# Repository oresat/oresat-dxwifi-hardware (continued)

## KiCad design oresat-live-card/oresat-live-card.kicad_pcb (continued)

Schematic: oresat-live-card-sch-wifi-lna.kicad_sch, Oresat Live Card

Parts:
C90, C91, C93: 15p; 0402-C-NOSILK; MPN GJM1555C1H150JB01D
C92: 1u; 0603-C-NOSILK; MPN GRT188R71E105KE13D
C106, C111: 100n; 0603-C-NOSILK; MPN C0603C104K5RACAUTO
C107, C114: 100p; 0402-C-NOSILK; MPN GCM1555C1H101GA16D
C108: 1n; 0402-C-NOSILK; MPN C0402C102J1GACTU
C109: 1n; 0402-C-NOSILK; MPN CGA2B2NP01H102J050BA
C110: 1p; 0402-C-NOSILK; MPN GCM1555C1H1R0CA16J
C112, C113: 100n; 0402-C-NOSILK; MPN CGA2B3X7R1E104K050BB
D15: GRN; LED-0603; MPN 150060GS75000
FL1, FL2: QPQ1907SR; MPN QPQ1907SR
L3: 18n; 0603-C-NOSILK; MPN 0603DC-18NXJRW
L4: 1.5n; 0402-C-NOSILK; MPN 0402HM-1N5EKTS
R85: 4.7k; 0603-C-NOSILK; MPN RMCF0603FT4K70
R88: 10k; 0603-C-NOSILK; MPN RMCF0603FT10K0
R105: 33k; 0603-C-NOSILK; MPN RMCF0603FT33K0
R106: 0; 0402-C-NOSILK; MPN RMCF0402ZT0R00
R109: 56; 0603-C-NOSILK; MPN ERJ-3EKF56R0V
R118, R119, R120: 4.99k; 0603-C-NOSILK; MPN RMCF0603FT4K99
R121: 100; 0603-C-NOSILK; MPN RMCF0603FT100R
TP26: TEST-POINT3X4; TestPoint-0.75mm-th
U18: TQP3M9037; DFN-8-1EP_2x2mm_P0.5mm_EP0.8x1.6mm; MPN TQP3M9037
U27: PAT1220-C-3DB; RF_Attenuator_Susumu_PAT1220; MPN PAT1220-C-3DB-T5
U28: PD2328J5050S2HF; MPN PD2328J5050S2HF
U29: LTC5538; DFN-8-1EP_3x3mm_P0.5mm_EP1.65x2.38mm; MPN LT5538IDD#TRPBF

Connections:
5VA: C106.2, C107.1, C112.2, C113.2, C114.1, R106.2, R118.1, U29.5 (VCC); also elsewhere on the board
/SIP B: ADC + Crystals/RF/RX_IN_DETECTED: C111.1, R119.2, R120.2, TP26.1 (1_1); also elsewhere on the board
/WiFi LNA/AR9271_RX: R121.1, U28.4 (OUTPUT1); also elsewhere on the board
/WiFi LNA/LNA_SHUTDOWN: R85.1, R105.1; also elsewhere on the board
/WiFi LNA/RX_FROM_SWITCH: FL1.1 (INPUT); also elsewhere on the board
GND: C91.2, C92.2, C106.1, C107.2, C108.2, C110.1, C111.2, C114.2, D15.1 (K), FL1.2 (GND), FL1.3 (GND), FL1.5 (GND), FL2.2 (GND), FL2.3 (GND), FL2.5 (GND), R88.2, R109.2, R120.1, U18.9 (GND), U27.3, U28.1 (GND), U28.3 (GND), U28.5 (GND), U29.4 (GND), U29.9 (GND); also elsewhere on the board
unnamed: C91.1, C92.1, L3.1, R106.1
unnamed: C93.2, U27.1
unnamed: C109.1, L4.2, R109.1
unnamed: D15.2 (A), R85.2
unnamed: C90.1, FL1.4 (OUTPUT)
unnamed: FL2.1 (INPUT), U27.2
unnamed: FL2.4 (OUTPUT), U28.2 (INPUT)
unnamed: C90.2, U18.2 (RF_IN)
unnamed: C93.1, L3.2, U18.7 (RF_OUT)
unnamed: R88.1, R105.2, U18.6 (SHUT_DOWN)
unnamed: C110.2, L4.1, R121.2, U28.6 (OUTPUT2)
unnamed: C113.1, U29.7 (CAP+)
unnamed: C112.1, U29.6 (CAP-)
unnamed: R118.2, U29.1 (EN)
unnamed: C109.2, U29.2 (IN+)
unnamed: C108.1, U29.3 (IN-)
unnamed: R119.1, U29.8 (OUT)

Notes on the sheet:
~ 1.65 V max which is < 1.8 V of Octavo ADC max
0402
Changed from 100 to 56
~ 3 V max
RF Detector, transforms RF detected into a DC sense line for Octavo to read
All resistors 0603 +/- 1% unless marked and AEQ certified unless otherwise marked. All caps are 0603 10% X5R or better and Vw >= 25 V and AEQ certified unless otherwise marked.
"LNA OFF"

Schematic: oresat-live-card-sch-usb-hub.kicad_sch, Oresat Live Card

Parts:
C1, C27, C28, C42, C54, C55, C56, C57, C58, C59, C60, C65, C66, C67, C68, C70, C71, C72: 100n; 0603-C-NOSILK; MPN C0603C104K5RACAUTO
C53, C69, C76, C96, C97: 10u; 0805-C-NOSILK; MPN GRT21BC71E106KE13K
C63, C64: 18p; 0603-C-NOSILK; MPN C0603C120J1GACTU
C73: 1u; 0603-C-NOSILK; MPN GRT188R71E105KE13D
D10: GRN; LED-0603; MPN 150060GS75000
FB1, FB3: BLM18KG300JH1D; 0603; MPN BLM18KG300JH1D
FB4, FB5: MMZ1608Y221BTD25; 0603; MPN MMZ1608Y221BTD25
R6, R7, R21, R59, R76, R77, R79, R89, R90, R91: 10k; 0603-C-NOSILK; MPN RMCF0603FT10K0
R29: 4.7k; 0603-C-NOSILK; MPN RMCF0603FT4K70
R78: 9.53k; 0603-C-NOSILK; MPN RMCF0603FT9K53
R83: 90.9k; 0603-C-NOSILK; MPN RMCF0603FT90K9
R98, R99: 0; 0603-C-NOSILK; MPN RMCF0603ZT0R00
TP1, TP15: TEST-POINT; TestPoint_Pad_D1.0mm
TP16, TP17, TP18: TEST-POINT3X4; TestPoint_Pad_D1.0mm
U2: TUSB4020BI; TQFP-48-1EP_7x7mm_P0.5mm_EP5x5mm; MPN TUSB4020BIPHPRQ1
U9, U20: TPS2041BQDBVRQ1; DBV5; MPN TPS2041BQDBVRQ1
Y3: 24MHz; 5X3.2-4SMD; MPN ECS-240-12-30BQ-AEN-TR

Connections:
1.1V: FB4.2; also elsewhere on the board
+3.3V: FB5.2, R6.2, R7.2, R77.1, R90.2, R91.2; also elsewhere on the board
+5V: R83.1, R98.2, R99.2; also elsewhere on the board
/SIP B: ADC + Crystals/UP_N: U2.27 (USB_DM_UP); also elsewhere on the board
/SIP B: ADC + Crystals/UP_P: U2.26 (USB_DP_UP); also elsewhere on the board
/SIP C: SD + eMMC + CAN/GRSTz: R89.2, U2.11 (GRSTz); also elsewhere on the board
/USB HUB/CAMERA_USB_N: U2.42 (USB_DM_DN1); also elsewhere on the board
/USB HUB/CAMERA_USB_P: U2.41 (USB_DP_DN1); also elsewhere on the board
/USB HUB/CAMERA_VUSB: FB3.2, TP1.1 (1_1); also elsewhere on the board
/USB HUB/WIFI_ENABLE: R29.1; also elsewhere on the board
/USB HUB/WIFI_STATUS: D10.1 (K); also elsewhere on the board
/USB HUB/WIFI_USB_N: U2.15 (USB_DM_DN2); also elsewhere on the board
/USB HUB/WIFI_USB_P: U2.14 (USB_DP_DN2); also elsewhere on the board
/USB HUB/WIFI_VUSB: FB1.2, R21.1, R29.2, TP15.1 (1_1); also elsewhere on the board
GND: C1.2, C27.2, C28.2, C42.2, C53.2, C54.2, C55.2, C56.2, C57.2, C58.2, C59.2, C60.2, C63.2, C64.2, C65.2, C66.2, C67.2, C68.2, C69.2, C70.2, C71.2, C72.2, C73.2, C76.2, C96.2, C97.2, R59.1, R76.1, R78.2, R79.1, R89.1, U2.10 (TEST), U2.49 (GND), U9.2 (GND), U20.2 (GND), Y3.2 (G), Y3.4 (G); also elsewhere on the board
unnamed: D10.2 (A), R21.2
unnamed: R59.2, U2.36 (FULLPWRMGMTz/SMBA1)
unnamed: R79.2, U2.35 (GANGED/SMBA2/HS_UP)
unnamed: R6.1, U2.5 (OVERCUR1z), U9.3 (~OC)
unnamed: R91.1, U2.8 (OVERCUR2z), U20.3 (~OC)
unnamed: R7.1, U2.4 (PWRCTL1/BATEN1), U9.4 (~EN)
unnamed: R90.1, U2.6 (PWRCTL2/BATEN2), U20.4 (~EN)
unnamed: R77.2, U2.21 (PWRCTL_POL)
unnamed: TP17.1 (1_1), U2.2 (SCL/SMBCLK)
unnamed: TP16.1 (1_1), U2.3 (SDA/SMBDAT)
unnamed: TP18.1 (1_1), U2.22 (SMBUSz)
unnamed: R78.1, U2.24 (USB_R1)
unnamed: R76.2, R83.2, U2.9 (USB_VBUS)
unnamed: C63.1, U2.38 (XI), Y3.1
unnamed: C64.1, U2.39 (XO), Y3.3
unnamed: C1.1, R98.1, U9.5 (IN)
unnamed: C27.1, C53.1, C96.1, FB3.1, U9.1 (OUT)
unnamed: C28.1, R99.1, U20.5 (IN)
unnamed: C42.1, C76.1, C97.1, FB1.1, U20.1 (OUT)
VDD: C54.1, C55.1, C57.1, C59.1, C65.1, C67.1, C69.1, FB4.1, U2.1 (VDD), U2.12 (VDD), U2.18 (VDD), U2.30 (VDD), U2.34 (VDD), U2.45 (VDD)
VDD33: C56.1, C58.1, C60.1, C66.1, C68.1, C70.1, C71.1, C72.1, C73.1, FB5.1, U2.7 (VDD33), U2.13 (VDD33), U2.23 (VDD33), U2.25 (VDD33), U2.33 (VDD33), U2.37 (VDD33), U2.40 (VDD33), U2.48 (VDD33)

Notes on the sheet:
Wifi USB
Ordering of ferrite bead and capacitor taken from TPS2041 datasheet (see figure 9-13)
Assert GRSTz via GPIO to deactivate USB hub and clear registers
Camera USB
"WIFI"
All resistors 0603 +/- 1% unless marked and AEQ certified unless otherwise marked. All caps are 0603 10% X5R or better and Vw >= 25 V and AEQ certified unless otherwise marked.

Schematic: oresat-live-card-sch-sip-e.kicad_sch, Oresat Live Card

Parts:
U7: OSD3358-1G-ISM; U-Octavo-OSD335X-BGA-256; MPN OSD3358-1G-ISM

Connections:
GND: U7.D8 (DGND@1), U7.D9 (DGND@2), U7.E5 (DGND@3), U7.E6 (DGND@4), U7.E7 (DGND@5), U7.E8 (DGND@6), U7.E9 (DGND@7), U7.E10 (DGND@8), U7.E11 (DGND@9), U7.E12 (DGND@10), U7.F5 (DGND@11), U7.F12 (DGND@12), U7.G5 (DGND@13), U7.G12 (DGND@14), U7.H4 (DGND@15), U7.H5 (DGND@16), U7.H12 (DGND@17), U7.H13 (DGND@18), U7.J4 (DGND@19), U7.J5 (DGND@20), U7.J12 (DGND@21), U7.J13 (DGND@22), U7.K5 (DGND@23), U7.K12 (DGND@24), U7.L5 (DGND@25), U7.L12 (DGND@26), U7.M5 (DGND@27), U7.M6 (DGND@28), U7.M7 (DGND@29), U7.M8 (DGND@30), U7.M9 (DGND@31), U7.M10 (DGND@32), U7.M11 (DGND@33), U7.M12 (DGND@34), U7.N8 (DGND@35), U7.N9 (DGND@36); also elsewhere on the board

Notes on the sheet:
All resistors 0603 +/- 1% unless marked and AEQ certified unless otherwise marked. All caps are 0603 10% X5R or better and Vw >= 25 V and AEQ certified unless otherwise marked.

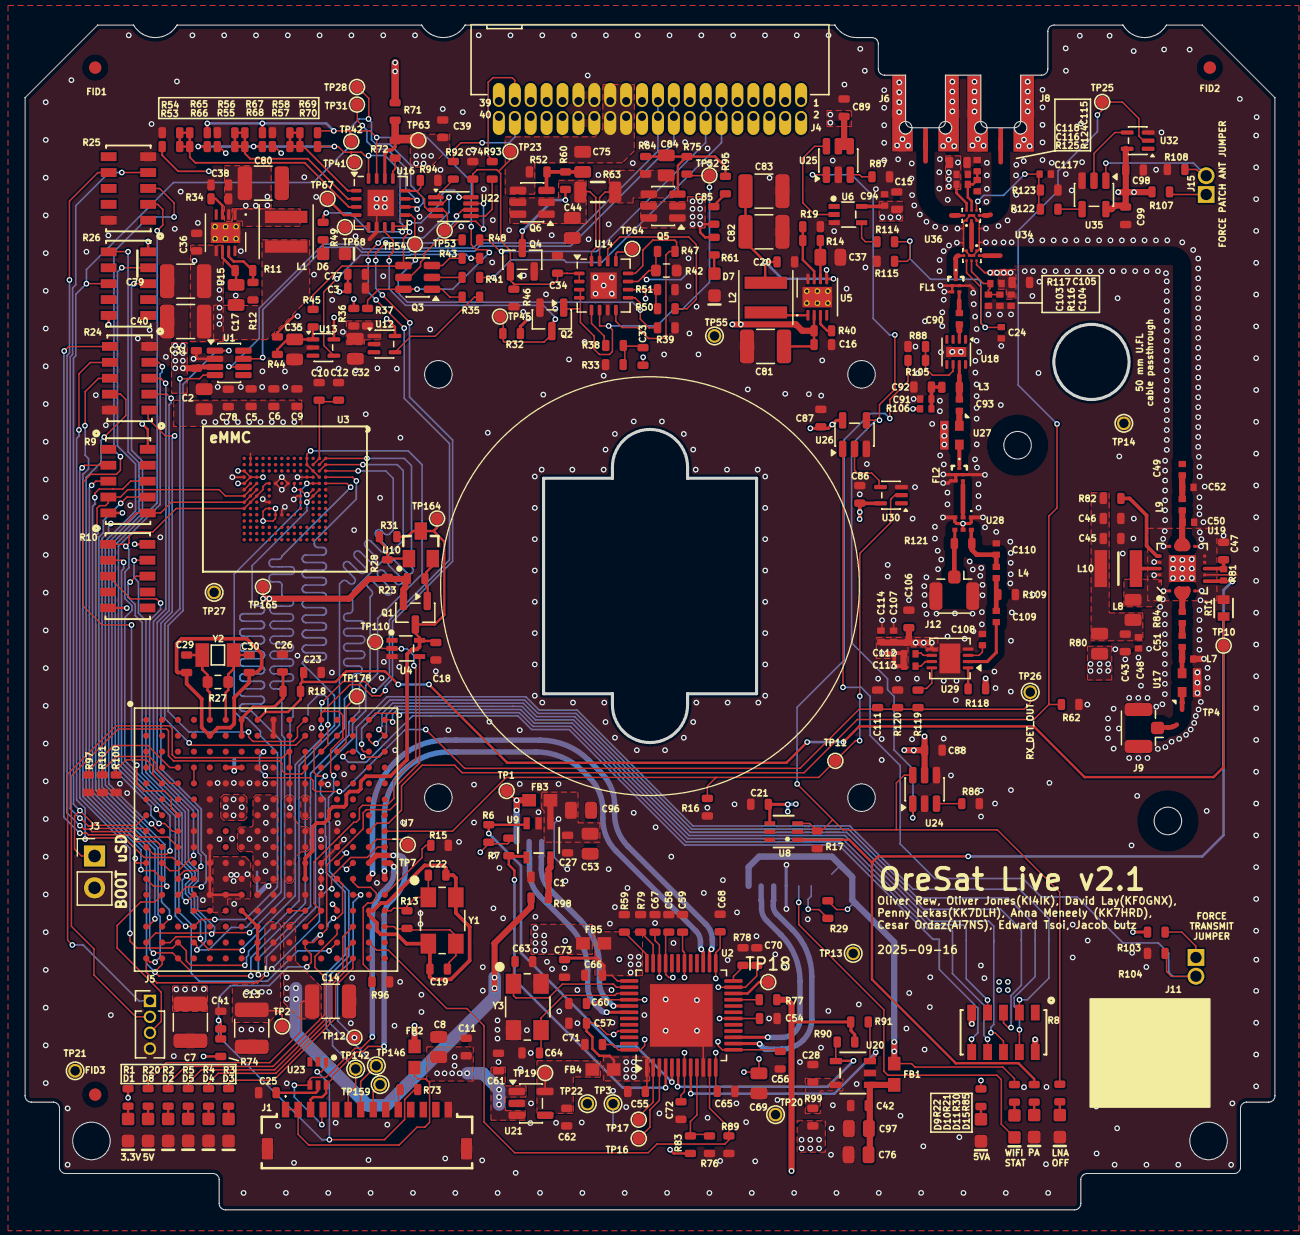
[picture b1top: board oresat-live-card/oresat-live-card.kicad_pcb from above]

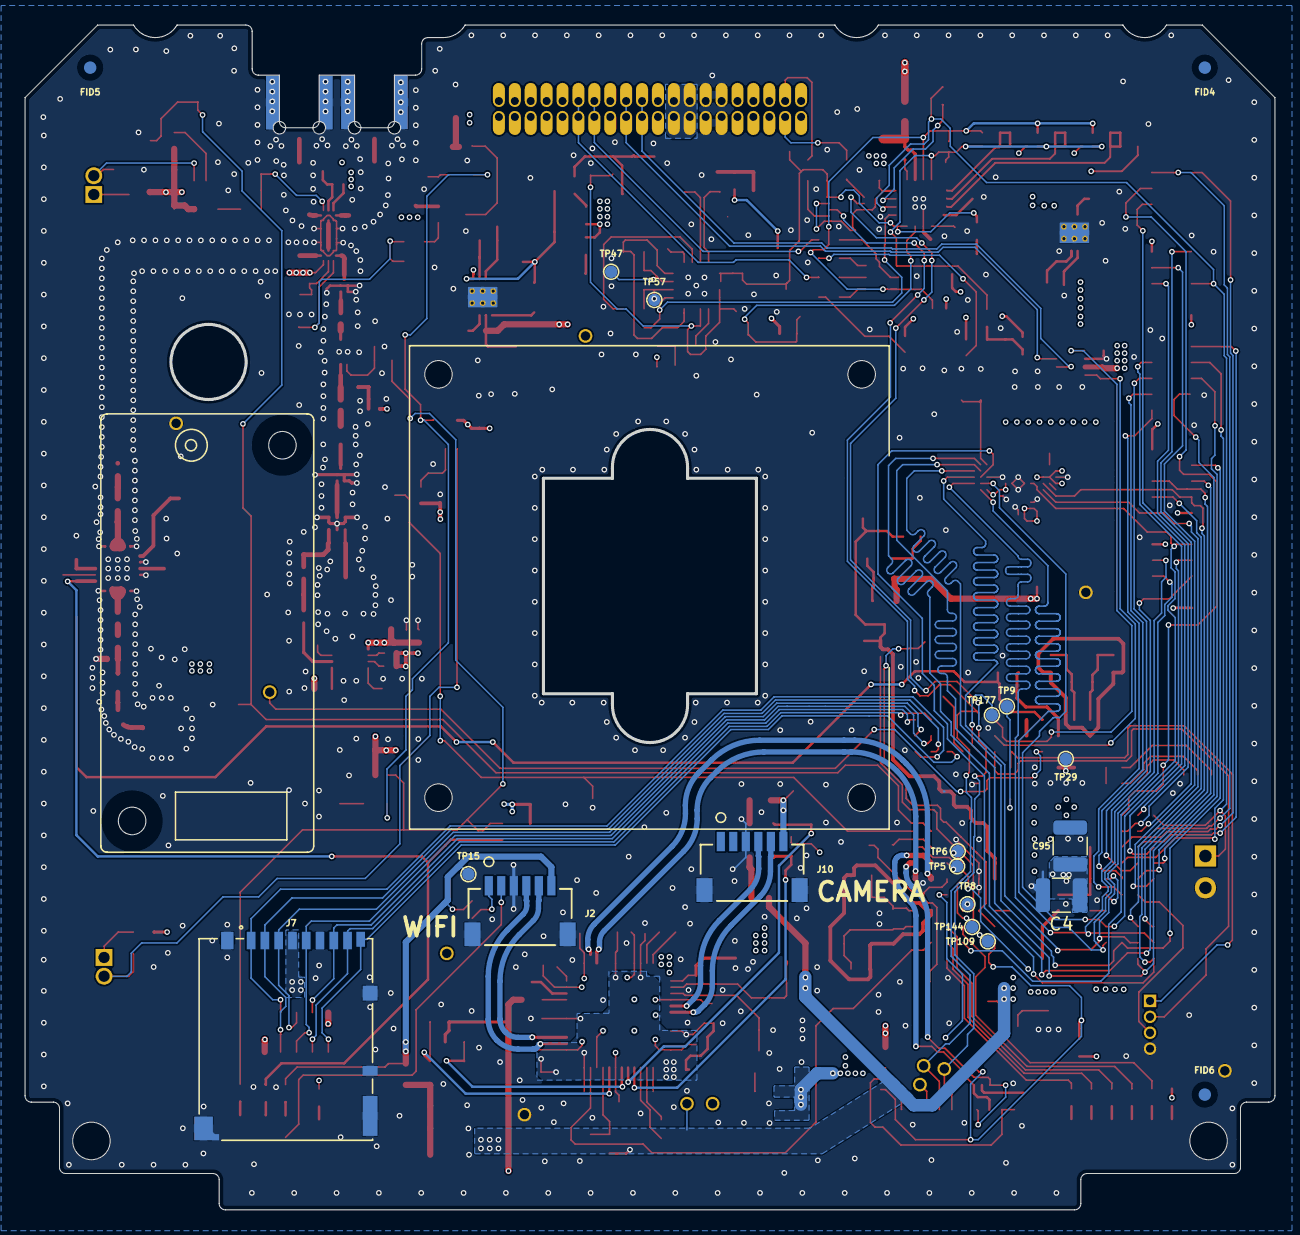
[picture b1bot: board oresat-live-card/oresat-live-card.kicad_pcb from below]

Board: 4 copper layers, 99.8 x 94.6 mm, 378 parts (20 on the bottom side), 246 nets.

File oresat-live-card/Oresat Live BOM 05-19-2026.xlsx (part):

Qty | Reference | Value | MFR | MPN | Description | DIS | DPN |  | ALT DIS | ALT DPN
49 | C1,C3,C4,C7,C11,C15,C16,C18,C20,C21,C23,C26,C28,C31,C36,C38,C39,C41,C42,C43,C45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 | 100n | TDK Corporation | CGA3E2X7R1E104K080AA | CAP CER 0.1UF 25V X7R 0603 | DigiKey | 445-5667-1-ND
1 | C110 | 1p | Murata Electronics | GCM1555C1H1R0CA16J | CAP CER 1PF 50V C0G/NP0 0402 | DigiKey | 490-17745-1-ND
2 | C112,C113 | 100n | TDK Corporation | CGA2B3X7R1E104K050BB | CAP CER 0.1UF 25V X7R 0402 | DigiKey | 445-6902-1-ND
9 | C13,C14,C40,C79,C80,C81,C82,C83,C95 | 22u | TDK Corporation | CGA6P1X7R1C226M250AC | CAP CER 22UF 16V X7R 1210 | DigiKey | 445-5723-1-ND
2 | C17,C37 | 2u2 | Murata Electronics | GRM188Z71C225ME43J | CAP CER 2.2UF 16V X7R 0603 | DigiKey | 490-GRM188Z71C225ME43JCT-ND
6 | C19,C22,C29,C30,C63,C64 | 12p | TDK Corporation | CGA3E2C0G1H120J080AA | CAP CER 12PF 50V C0G 0603 | DigiKey | 445-5629-1-ND
8 | C2,C8,C27,C44,C53,C69,C75,C76 | 10u | TDK Corporation | CGA4J1X7S1C106M125AC | CAP CER 10UF 16V X7S 0805 | DigiKey | 445-16111-1-ND
10 | C24,C49,C94,C103,C104,C107,C114,C115,C116,C117 | 100p | Murata Electronics | GCM1555C1H101GA16D | CAP CER 100PF 50V C0G/NP0 0402 | DigiKey | 490-GCM1555C1H101GA16DCT-ND
2 | C32,C35 | 1u | TDK Corporation | CGA4J2X7R1C105K125AA | CAP CER 1UF 16V X7R 0805 | DigiKey | 445-5689-1-ND
3 | C48,C108,C109 | 1n | TDK Corporation | CGA2B2NP01H102J050BA | CAP CER 1000PF 50V NP0 0402 | DigiKey | 445-12118-1-ND
13 | C5,C6,C9,C10,C12,C33,C34,C61,C62,C73,C78,C84,C85 | 1u | TDK Corporation | CGA3E1X7R1C105K080AC | CAP CER 1UF 16V X7R 0603 | DigiKey | 445-12539-1-ND
1 | C50 | 3p | KYOCERA AVX | 04025U3R0BAT2A | CAP CER 3PF 50V NP0 0402 | Mouser | 581-04025U3R0BAT2A
1 | C51 | 1.4p | KYOCERA AVX | 04025J1R4PBSTR\500 | CAP 50V 1.4pF .02pFTol ThinFilm 0402 | Mouser | 581-04025J1R4PBSTR5
1 | C52 | 1.6p | KYOCERA AVX | 04025U1R6BAT2A | CAP CER 1.6PF 50V NP0 0402 | Mouser | 581-04025U1R6BAT2A
3 | C90,C91,C93 | 15p | Murata Electronics | GJM1555C1H150JB01D | CAP CER 15PF 50V C0G/NP0 0402 | DigiKey | 490-3117-1-ND
1 | C92 | 1u | Taiyo Yuden | EMK105BJ105KVHF | CAP CER 1UF 16V X5R 0402 | DigiKey | 587-3709-1-ND
8 | D1,D6,D7,D8,D9,D10,D11,D15 | GRN | Würth Elektronik | 150060GS75020 | Green 525nm LED 3.2V 0603 | DigiKey | 732-150060GS75020CT-ND
4 | D2,D3,D4,D5 | BLUE | Würth Elektronik | 150060BS75020 | Blue 470nm LED 3.2V 0603 | DigiKey | 732-150060BS75020CT-ND
3 | FB1,FB2,FB3 | BLM18KG300TH1D | Murata Electronics | BLM18KG300JH1D | FERRITE BEAD 30 OHM 0603 1 LN | DigiKey | 490-13263-1-ND
2 | FB4,FB5 | MMZ1608Y221BTD25 | TDK Corporation | MMZ1608Y221BTD25 | FERRITE BEAD 220 OHM 0603 1LN | DigiKey | 445-MMZ1608Y221BTD25CT-ND
2 | FL1,FL2 | QPQ1907SR | Qorvo | QPQ1907SR | 2.4GHZ WI-FI LTE COEXBOOST BAW F | DigiKey | 2312-QPQ1907SRCT-ND
1 | J1 | ORESAT-DEBUG-CONNECTOR | TE Connectivity AMP Connectors | 2-1734592-0 | CONN FPC BOTTOM 20POS 0.50MM R/A | DigiKey | A100287CT-ND |  | Mouser | 571-2-1734592-0
2 | J11,J15 | 2X1_TH_JUMPER
1 | J14 | Conn_01x02 |  |  | Generic connector, single row, 01x02, script generated (kicad-library-utils/sch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
2 | J2,J10 | SM06B-SRSS-TB | JST Commercial | SM06B-SRSS-TB | CONN HEADER SMD R/A 6POS 1MM | DigiKey | 455-SM06B-SRSS-TBCT-ND
1 | J4 | TFM-120-01-L-D-RA | Samtec Inc. | TFM-120-01-L-D-RA | CONN HEADER R/A 40POS 1.27MM | DigiKey | On Reels
2 | J6,J8 | SMPM | TE Connectivity Linx | 2477330-1 | CONN SMPM PLUG STR 50OHM EDGEMNT | DigiKey | 343-2477330-1CT-ND
1 | J7 | DM3BT-DSF-PEJS | Hirose Electric Co Ltd | DM3BT-DSF-PEJS | CONN MICRO SD CARD R/A SMD | DigiKey | HR1942CT-ND
2 | J9,J12 | U.FL | Hirose Electric Co Ltd | U.FL-R-SMT-1(10) | CONN U.FL RCPT STR 50 OHM SMD | DigiKey | H11891CT-ND
2 | L1,L2 | 3u3 | Coilcraft | XGL4020-332MEC | FIXED IND 3.3UH 6.6A 34MOHM SMD | DigiKey | 2457-XGL4020-332MEC-ND
1 | L10 | 10n | Coilcraft | 1008HQ-10NXJLC | Fixed Inductors 1008 10nH Unshld 5% | Coilcraft | 1008HQ-10NXJLC
1 | L3 | 18nH | Coilcraft | 0603DC-18NXJRW | FIXED IND 18NH 2A 78 MOHM SMD | DigiKey | 2457-0603DC-18NXJRW-ND |  | Mouser | 994-0603DC-18NXJRW
1 | L4 | 1.5n | Delta Electronics/Components | 0402HM-1N5EKTS | FIXED IND 1.5NH 1A 30 MOHM SMD | DigiKey | 2035-1382-1-ND
1 | L7 | 1.7n | Coilcraft | 0402DC-1N7XJRW | 1.7nH RF Inductor, ceramic core, 5% tol | DigiKey | 2457-0402DC-1N7XJRW-ND |  | Mouser | 994-0402DC-1N7XJRW
1 | L8 | 6.8n. | Coilcraft | 0805CS-060XJRC | FIXED IND 6.8NH 600MA 110MOHM SM | DigiKey | 2457-0805CS-060XJRC-ND
1 | L9 | 1.0n | TDK Corporation | MLK1005S1N0ST000 | FIXED IND 1NH 500MA 100 MOHM SMD | DigiKey | 445-MLK1005S1N0ST000CT-ND
1 | PCB1 | ORESAT-CARD-V1.3-GENERIC-1RF-POS1 | N/A | N/A | N/A | N/A | N/A
1 | PCBA1 | WF-NP9202WF | Unknown | Unknown | AR9271 USB to WiFi daughter board | N/A | N/A
1 | Q1 | PMMBT2907A | Nexperia USA Inc. | PMBT2907A,215 | TRANS PNP 60V 0.6A TO-236AB | DigiKey | 1727-2958-1-ND |  | Mouser | 771-PMBT2907T/R
2 | Q2,Q4 | DMN3028 | Diodes Incorporated | DMN3028LQ-7 | MOSFET BVDSS: 25V~30V,SOT23 | DigiKey | 31-DMN3028LQ-7CT-ND
1 | Q3 | DMP2240UDM | Diodes Incorporated | DMP2240UDM-7 | Dual PMOS transistor, 6 pin package | DigiKey | DMP2240UDMDICT-ND
2 | Q5,Q6 | DMPH2040 | Diodes Incorporated | DMPH2040UVTQ-7 | MOSFET P-CH 20V 5.6/11.7A TSOT26 | DigiKey | 31-DMPH2040UVTQ-7CT-ND
12 | R1,R2,R3,R4,R5,R20,R22,R29,R30,R49,R51,R85 | 4.7k | Panasonic | ERJ-3EKF4701V | RES SMD 4.7K OHM 1% 1/10W 0603 | DigiKey | P4.70KHCT-ND
1 | R105 | 33k | Panasonic | ERJ-U03F3302V | RES 33K OHM 1% 1/10W 0603 | DigiKey | 10-ERJ-U03F3302VCT-ND
1 | R106 | 0 | Panasonic | ERJ-2GE0R00X | RES SMD 0 OHM JUMPER 1/10W 0402 | DigiKey | P0.0JCT-ND
1 | R109 | 56 | Panasonic | ERJ-3EKF56R0V | RES SMD 56 OHM 1% 1/10W 0603 | DigiKey | P56.0HCT-ND
5 | R11,R12,R14,R19,R33 | 100k | Panasonic | ERJ-3EKF1003V | RES SMD 100K OHM 1% 1/10W 0603 | DigiKey | P100KHCT-ND
2 | R115,R123 | 5.62k | Panasonic | ERJ-3EKF5621V | RES SMD 5.62K OHM 1% 1/10W 0603 | DigiKey | P5.62KHCT-ND
2 | R116,R124 | 5.62k | Panasonic | ERJ-2RKF5621X | RES SMD 5.62K OHM 1% 1/10W 0402 | DigiKey | P5.62KLCT-ND
2 | R117,R125 | 10k | Panasonic | ERJ-2RKF1002X | RES SMD 10K OHM 1% 1/10W 0402 | DigiKey | P10.0KLCT-ND
3 | R118,R119,R120 | 4.99k | Panasonic | ERJ-3EKF4991V | RES SMD 4.99K OHM 1% 1/10W 0603 | DigiKey | P4.99KHCT-ND
3 | R13,R36,R44 | 1M | Panasonic | ERJ-3EKF1004V | RES SMD 1M OHM 1% 1/10W 0603 | DigiKey | P1.00MHCT-ND
1 | R23 | 499 | Panasonic | ERJ-3EKF4990V | RES SMD 499 OHM 1% 1/10W 0603 | DigiKey | P499HCT-ND
3 | R24,R25,R26 | 100k | Panasonic | EXB-A10P104J | RES ARRAY 8 RES 100K OHM 2512 | DigiKey | U7104CT-ND
1 | R31 | 40.2K | Panasonic | ERJ-3EKF4022V | RES SMD 40.2K OHM 1% 1/10W 0603 | DigiKey | P40.2KHCT-ND
2 | R35,R43 | 665k | Panasonic | ERJ-3EKF6653V | RES SMD 665K OHM 1% 1/10W 0603 | DigiKey | P665KHCT-ND
2 | R37,R45 | 330k | Panasonic | ERJ-3EKF3303V | RES SMD 330K OHM 1% 1/10W 0603 | DigiKey | P330KHCT-ND
6 | R41,R48,R71,R92,R93,R121 | 100 | Panasonic | ERJ-3EKF1000V | RES SMD 100 OHM 1% 1/10W 0603 | DigiKey | P100HCT-ND
8 | R47,R59,R60,R94,R96,R98,R99,R100 | 0 | Panasonic | ERJ-3GEY0R00V | RES SMD 0 OHM JUMPER 1/10W 0603 | DigiKey | P0.0GCT-ND
6 | R54,R55,R57,R95,R103,R107 | 1k | Panasonic | ERJ-3EKF1001V | RES SMD 1K OHM 1% 1/10W 0603 | DigiKey | P1.00KHCT-ND
33 | R6,R7,R15,R16,R17,R18,R21,R28,R32,R34,R38,R39,R40,R46,R50,R52,R61,R62,R64,R72,R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 | 10k | Panasonic | ERJ-3EKF1002V | RES SMD 10K OHM 1% 1/10W 0603 | DigiKey | P10.0KHCT-ND
1 | R63 | 100m | Panasonic | ERJ-8BWFR100V | RES 0.1 OHM 1% 1W 1206 | DigiKey | P.10AUCT-ND
1 | R78 | 9.53k | Panasonic | ERJ-3EKF9531V | RES 9.53K OHM 1% 1/10W 0603 | DigiKey | P9.53KHCT-ND
3 | R8,R9,R10 | 10k | Panasonic | EXB-A10P103J | RES ARRAY 8 RES 10K OHM 2512 | DigiKey | U7103CT-ND
1 | R80 | 0 | Panasonic | ERJ-6GEY0R00V | RES SMD 0 OHM JUMPER 1/8W 0805 | DigiKey | P0.0ACT-ND
1 | R81 | 110 | Panasonic | ERJ-2RKF1100X | RES SMD 110 OHM 1% 1/10W 0402 | DigiKey | P110LCT-ND
1 | R82 | 220 | Panasonic | ERJ-3EKF2200V | RES SMD 220 OHM 1% 1/10W 0603 | DigiKey | P220HCT-ND
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
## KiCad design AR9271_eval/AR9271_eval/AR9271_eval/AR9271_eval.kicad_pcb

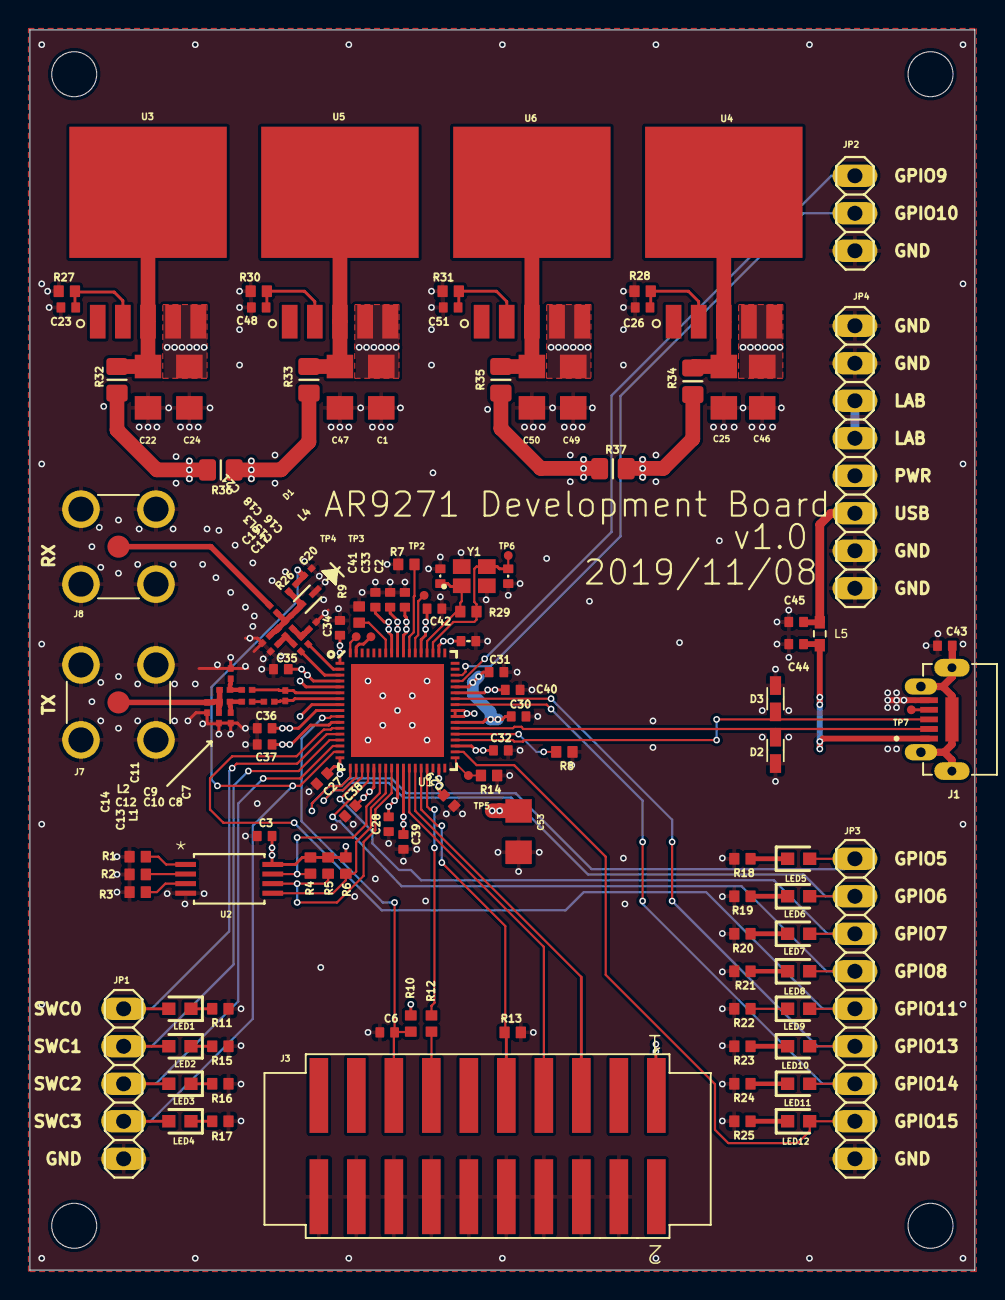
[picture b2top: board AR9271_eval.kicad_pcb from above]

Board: 4 copper layers, 64.0 x 84.0 mm, 135 parts (0 on the bottom side), 80 nets.

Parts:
C1, C22, C24, C25, C46, C47, C49, C50, C53: 4.7uF; C1206_334
C2, C3, C6, C26, C27, C28, C29, C30, C31, C32, C33, C34, C43, C45, C51: 100n; .0402-B-NOSILK
C4, C5, C35, C36: 10p; .0402-B-NOSILK
C7: 2.2pF; .0201-B-NOSILK
C8, C9, C15, C16, C20: 10.0pF; .0201-B-NOSILK
C10, C11, C12, C13: 2.0pF; .0201-B-NOSILK
C14, C19: 1.0pF; .0201-B-NOSILK
C17, C18: 1.5pF; .0201-B-NOSILK
C21: 100.0pF; .0201-B-NOSILK
C23, C48: 10nF; .0402-B-NOSILK
C37: 100p; .0402-B-NOSILK
C38, C40: 1n; .0402-B-NOSILK
C39, C44: 10n; .0402-B-NOSILK
C41, C42, C52: 1u; .0402-B-NOSILK
D1: SMP1321-079LF; SOD523
D2, D3: PGB1010603MR; ESD_PGB1010603MR
H1, H2, H3, H4: STAND-OFFTIGHT; STAND-OFF-TIGHT_519
J1: UJ2-MIBH2-4-SMT-TR; CUI_UJ2-MIBH2-4-SMT-TR
J3: HTST-110-01-XX-DV
J7, J8: 132134-15; AMPHENOL_132134-15
JP1: 1X05_325
JP2: 1X03_325
JP3: 1X09_325
JP4: 1X08_325
L1, L2: 1.8nH; .0201-B-NOSILK
L3, L4: 2.2nH; .0201-B-NOSILK
L5: BLM18PG221SH1D; INDC1608X95
LED1, LED2, LED3, LED4, LED5, LED6, LED7, LED8, LED9, LED10, LED11, LED12: LTST-C193KGKT-5A; LEDC1607X80N
R1: DNP; .0402-A-NOSILK
R2, R3: 0; .0402-A-NOSILK
R4, R7, R10, R13, R14: 10k; .0402-A-NOSILK
R5, R6: 4.7k; .0402-A-NOSILK
R8: 51.1; .0402-A-NOSILK
R9: 6.19k; .0402-A-NOSILK
R11, R15, R16, R17, R18, R19, R20, R21, R22, R23, R24, R25: 510; .0402-A-NOSILK
R12: 33; .0402-A-NOSILK
R26: 1.0k; .0201-B-NOSILK
R27, R30: 330k; .0402-A-NOSILK
R28, R31: 120k; .0402-A-NOSILK
R29: 1M; .0402-A-NOSILK
R32, R33, R34, R35: 0; .0805-B
R36, R37: DNP; .0805-B
TP2, TP3, TP4, TP5, TP6, TP7: TPTP06R; TP06R_385
U1: U-ATHEROS-AR9271; QFN-68
U2: AT24C04C-XHM-T; 8X
U3, U4, U5, U6: LT3080EQPBF; DDPAK-5_Q
Y1: ECS-400-10-36-CKY-TR; XTAL_ECS-400-10-36-CKY-TR

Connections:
1V2_A: C2.1, C41.1, C42.1, R35.2, R37.1, U1.56, U1.59, U1.61
1V2_D: C37.1, C38.1, C39.1, C40.1, R34.2, R37.2, U1.11, U1.22, U1.27, U1.42, U1.43, U1.46
3V3_A: C33.1, C34.1, C35.1, C36.1, C52.1, R33.2, R36.1, U1.1, U1.4, U1.9, U1.53, U1.60
3V3_D: C3.1, C27.1, C28.1, C29.1, C30.1, C31.1, C32.1, C53.1, J3.1, R4.2, R5.2, R6.2, R10.2, R32.2, R36.2, U1.5, U1.8, U1.17, U1.26, U1.33, U1.37, U1.41, U1.47, U2.8
A1: R2.2, U2.2
A2: R3.2, U2.3
BIASREF: R9.1, U1.62
CTRL1: R7.2, U1.58
CTRL2: TP2.TP, U1.57
EE-SCK: R5.1, U1.25, U2.6
EE-SDA: R6.1, U1.24, U2.5
EE-WP: R4.1, U1.23, U2.7
GND: C1.2, C2.2, C3.2, C4.2, C5.2, C6.2, C11.1, C13.1, C14.2, C17.2, C19.2, C20.2, C22.2, C23.2, C24.2, C25.2, C26.2, C27.2, C28.2, C29.2, C30.2, C31.2, C32.2, C33.2, C34.2, C35.2, C36.2, C37.2, C38.2, C39.2, C40.2, C41.2, C42.2, C43.2, C44.2, C45.2, C46.2, C47.2, C48.2, C49.2, C50.2, C51.2, C52.2, C53.2, D1.1, D2.2, D3.2, J1.5, J3.4, J3.6, J3.8, J3.10, J3.12, J3.14, J3.16, J3.18, J3.20, J7.P1, J7.P2, J7.P3, J7.P4, J8.P1, J8.P2, J8.P3, J8.P4, JP1.5, JP2.3, JP3.9, JP4.1, JP4.2, JP4.7, JP4.8, L1.1, L4.1, R1.1, R2.1, R3.1, R7.1, R8.1, R9.2, R11.1, R13.1, R14.1, R15.1, R16.1, R17.1, R18.1, R19.1, R20.1, R21.1, R22.1, R23.1, R24.1, R25.1, R27.1, R28.1, R30.1, R31.1, U1.69, U2.4, Y1.2, Y1.4
GPIO5: JP3.1, LED5.2, U1.18
GPIO6: JP3.2, LED6.2, U1.19
GPIO7: JP3.3, LED7.2, U1.20
GPIO8: JP3.4, LED8.2, U1.21
GPIO9: JP2.1, U1.48
GPIO10: JP2.2, U1.49
GPIO11: JP3.5, LED9.2, U1.12
GPIO13: JP3.6, LED10.2, U1.45
GPIO14: JP3.7, LED11.2, U1.44
GPIO15: JP3.8, LED12.2, U1.36
LDO_IN: C1.1, C24.1, C46.1, C49.1, JP4.5, U3.4, U3.5, U4.4, U4.5, U5.4, U5.5, U6.4, U6.5
unnamed: J1.4, TP7.TP
unnamed: JP4.3, JP4.4
unnamed: R1.2, U2.1
unnamed: LED1.1, R11.2
unnamed: LED2.1, R15.2
unnamed: C10.2, C12.1, L1.2
unnamed: C15.2, C17.1, L3.1
unnamed: C16.2, C18.1, L4.2
unnamed: C9.2, C11.2, L2.1
unnamed: LED3.1, R16.2
unnamed: LED4.1, R17.2
unnamed: LED5.1, R18.2
unnamed: C8.2, C10.1
unnamed: C23.1, R27.2, U3.2
unnamed: C18.2, C19.1, C21.1, D1.2, L3.2, R26.2
unnamed: C26.1, R28.2, U4.2
unnamed: LED6.1, R19.2
unnamed: LED7.1, R20.2
unnamed: LED8.1, R21.2
unnamed: LED9.1, R22.2
unnamed: C43.1, J1.SH1, J1.SH2, J1.SH3, J1.SH4, J1.SH5
unnamed: C22.1, R32.1, U3.3, U3.6
unnamed: LED10.1, R23.2
unnamed: LED11.1, R24.2
unnamed: LED12.1, R25.2
unnamed: C25.1, R34.1, U4.3, U4.6
unnamed: C48.1, R30.2, U5.2
unnamed: C47.1, R33.1, U5.3, U5.6
unnamed: C51.1, R31.2, U6.2
unnamed: C50.1, R35.1, U6.3, U6.6
PDET: TP4.TP, U1.68
RCV_IN: C21.2, J8.1
RFIN_N: C16.1, U1.2
RFIN_P: C15.1, U1.3
RFOUT_N: C7.1, C9.1, U1.6
RFOUT_P: C7.2, C8.1, U1.7
SPIBOOT: R14.2, TP5.TP, U1.35
SWCOM0: JP1.1, LED1.2, U1.13
SWCOM1: JP1.2, LED2.2, U1.14
SWCOM2: JP1.3, LED3.2, U1.15
SWCOM3: C20.1, JP1.4, LED4.2, R26.1, U1.16
TCK: J3.9, R13.2, U1.30
TDI: J3.5, U1.29
TDO: J3.13, R12.2
TDO-PRE-RES: R12.1, U1.31
TMS: J3.7, U1.28
TXRTUNE: R8.2, U1.39
USB+5V: C45.1, JP4.6, L5.2
USB_+V: C44.1, J1.1, L5.1
USB_DM: D2.1, J1.2, U1.40
USB_DP: D3.1, J1.3, U1.38
XMIT_OUT: C12.2, C13.2, C14.1, J7.1, L2.2
XPABIOS: TP3.TP, U1.67
XTALI: C4.1, R29.1, U1.55, Y1.1
XTALO: C5.1, R29.2, TP6.TP, U1.54, Y1.3
~RST: C6.1, J3.15, R10.1, U1.10

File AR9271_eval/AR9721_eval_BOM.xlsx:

Bill Of Materials for AR9721
Source file: AR9721_eval.sch
Last modified: 2019/09/17
PCB version: 1.0 |  |  | P/DNP = | Place/Do Not Place (DNP is for final production boards)
BOM revision: 0 |  |  | Generic = | Any generic part with the same characteristics are OK (e.g., bypass cap)
Cnt | Part References | P/DNP | Mfg | Mfg PN | Description | Generic | Dist | Dist Part Number
9 | C1, C22, C24, C25, C46, C47, C49, C50, C53 | P | Murata Electronics | GCM31CR71C475KA37L | Capacitor, 4.7uF, 1206 | Y | Digi-key | 490-6065-1-ND
4 | C10, C11, C12, C13 | P | Taiyo Yuden | UMK063CG020CTHF | Capacitor, 2pF, 0201 | Y | Digi-key | 587-3777-2-ND
2 | C14, C19 | P | Taiyo Yuden | UMK063CG010CTHF | Capacitor, 1pF, 0201 | Y | Digi-key | 587-3776-1-ND
2 | C17, C18 | P | Taiyo Yuden | UMK063CG1R5CT-F | Capacitor, 1.5pF, 0201 | Y | Digi-key | 587-3202-6-ND
15 | C2, C3, C6, C26, C27, C28, C29, C30, C31, C32, C33, C34, C43, C45, C51 | P | TDK | CGA2B1X7R1C104K050BC | Capacitor, 100nF, 0402 | Y | Digi-key | 445-5613-1-ND
1 | C21 | P | Taiyo Yuden | UMK063CG101JT-F | Capacitor, 100pF, 0201 | Y | Digi-key | 587-3207-2-ND
4 | C23, C39, C44, C48 | P | Kemet | C0402C103K4RACAUTO | Capacitor, 10nF, 0402 | Y | Digi-key | 399-6825-1-ND
1 | C37 | P | TDK | CGA2B2C0G1H101J050BA | Capacitor, 100pF, 0402 | Y | Digi-key | 445-5596-1-ND
2 | C38, C40 | P | Kemet | C0402C102K5GACTU | Capacitor, 1nF, 0402 | Y | Digi-key | 399-7756-1-ND
4 | C4, C5, C35, C36 | P | Yageo | CC0402JRNPO9BN100 | Capacitor, 10pF, 0402 | Y | Digi-key | 311-1014-1-ND
3 | C41, C42, C52 | P | TDK | CGA2B2C0G1H100D050BA | Capacitor, 1uF, 0402 | Y | Digi-key | 445-5584-1-ND
1 | C7 | P | Taiyo Yuden | UMK063CG2R2CTHF | Capacitor, 2.2pF, 0201 | Y | Digi-key | 587-5314-1-ND
5 | C8, C9, C15, C16, C20 | P | Taiyo Yuden | UMK063CG100DTHF | Capacitor, 10pF, 0201 | Y | Digi-key | 587-3785-2-ND
1 | D1 | P | Skyworks | SMP1321-079 | RF PIN Diode | N | Digi-key | 863-1099-1-ND
2 | D2, D3 | P | Littelfuse Inc. | PGB1010603MR | PGB1 Series 15 V 63 Bi-Directional SMT ESD TVS | Y | Digi-key | F2594CT-ND
1 | J1 | P | CUI Inc. | UJ2-MIBH2-4-SMT-TR | Micro B Type 5 Pin Horizontal SMT USB Jack 2.0 | Y | Digi-key | 102-4007-1-ND
1 | J3 | P | Samtec Inc. | HTST-110-01-L-DV-P | Conn Shrouded Header HDR 20 POS 2.54mm Solder ST SMD | Y | Digi-key | SAM15675-ND
2 | J7, J8 | P | Amphenol RF | 132134-15 | Rf Coaxial, Sma, Straight Jack, Pcb | Y | Digi-key | ACX1962-ND
4 | JP1, JP2, JP3, JP4 | P | NA | NA | PIN HEADER | Y | Digi-key | 952-3308-ND
2 | L1, L2 | P | Murata Electronics | LQP03TN1N8B02D | Inductor, 1.8nH, 0201 | Y | Digi-key | 490-6720-1-ND
2 | L3, L4 | P | Murata Electronics | LQP03TN2N2B02D | Inductor, 2.2nH, 0201 | Y | Digi-key | 490-6723-1-ND
1 | L5 | P | Murata Electronics | BLM18PG221SH1D | FERRITE BEAD 220 OHM 0603 1LN | N | Digi-key | 490-7817-1-ND
12 | LED1, LED2, LED3, LED4, LED5, LED6, LED7, LED8, LED9, LED10, LED11, LED12 | P | Lite-On | LTST-C193KGKT-5A | LED,Green,0603, | Y | Digi-key | 160-1828-1-ND
3 | R1, R36, R37 | NP | NA | NA | NA | NA | NA | NA
12 | R11, R15, R16, R17, R18, R19, R20, R21, R22, R23, R24, R25 | P | Panasonic | ERJ-2GEJ511X | Resistor, 510, 0402 | Y | Digi-key | P510JTR-ND
1 | R12 | P | Panasonic | ERJ-2GEJ330X | Resistor, 33, 0402 | Y | Digi-key | P33JCT-ND
2 | R2, R3 | P | Panasonic | ERJ-2GE0R00X | Resistor, 0, 0402 | Y | Digi-key | P0.0JCT-ND
1 | R26 | P | Panasonic | ERJ-1GNF1001C | Resistor, 1k, 0201 | Y | Digi-key | P122413CT-ND
2 | R27, R30 | P | Panasonic | ERJ-2RKF3303X | Resistor, 330k, 0402 | Y | Digi-key | P330KLCT-ND
2 | R28, R31 | P | Panasonic | ERJ-2RKF1203X | Resistor, 120k, 0402 | Y | Digi-key | P120KLCT-ND
1 | R29 | P | Panasonic | ERJ-2GEJ105X | Resistor, 1M, 0402 | Y | Digi-key | P1.0MJTR-ND
4 | R32, R33, R34, R35 | P | Panasonic | ERJ-6GEY0R00V | Resistor, 0, 0805 | Y | Digi-key | P0.0ACT-ND
5 | R4, R7, R10, R13, R14 | P | Panasonic | ERJ-2GEJ103X | Resistor, 10k, 0402 | Y | Digi-key | ERJ-2GEJ103X
2 | R5, R6 | P | Panasonic | ERJ-2GEJ103X | Resistor, 4.7k, 0402 | Y | Digi-key | P10KJCT-ND
1 | R8 | P | Panasonic | ERJ-2RKF51R1X | Resistor, 51.1, 0402 | Y | Digi-key | P51.1LCT-ND
1 | R9 | P | Panasonic | ERJ-2RKF6191X | Resistor, 6.19k, 0402 | Y | Digi-key | P6.19KLCT-ND
1 | U1 | P | Atheros | AR9271-AL1A | Atheros WiFi WLAN IC | N | AliExpress | N/A
1 | U2 | P | Microchip | AT24C04CXHMT | EEPROM with I2C interface | N | Digi-key | AT24C04C-XHM-TCT-ND
4 | U3, U4, U5, U6 | P | Analog Devices | LT3080EQ#PBF | Adj. 1.1A Single Res LDO Regulator | N | Digi-key | LT3080EQ#PBF-ND
1 | Y1 | P | ECS International | ECS-400-10-36-CKY-TR | Crystal 40mhz 10pf Smd | N | Digi-key | XC2666CT-ND
VERSION INFO
Rev | Date | Notes
1 | 43725 | First rev BOM

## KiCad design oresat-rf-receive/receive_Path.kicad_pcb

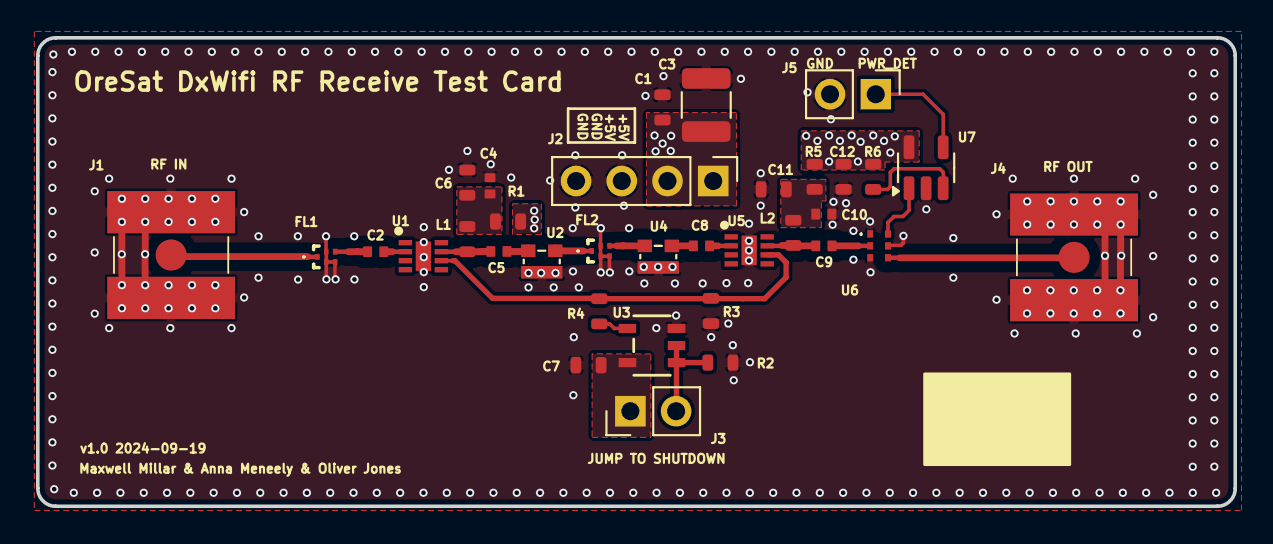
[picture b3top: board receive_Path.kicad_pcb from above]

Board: 4 copper layers, 66.5 x 26.0 mm, 34 parts (0 on the bottom side), 22 nets.

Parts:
C1: 2u2; 0603-C-NOSILK
C2, C4, C5, C8, C9, C10: 15p; 0402-C-NOSILK
C3: 22u; C_1210_3225Metric
C6, C11: 1u; 0603-C-NOSILK
C7, C12: 100n; 0603-C-NOSILK
FL1, FL2: QPQ1907SR
J1: 142-0711-201; SMA 142-0711-201
J2: 0022232041; PinHeader_1x04_P2.54mm_Vertical
J3, J5: 0022232021; PinHeader_1x02_P2.54mm_Vertical
J4: Conn_Coaxial_142-0711-201; SMA 142-0711-201
L1, L2: 18nH; 0603-C-NOSILK
R1, R5: 0; 0603-C-NOSILK
R2, R4: 10k; 0603-C-NOSILK
R3: 33K; 0603-C-NOSILK
R6: 10K; 0603-C-NOSILK
U1, U5: TQP3M9037
U2, U4: PAT1220-C-3DB; PAT1220(0805)
U3: SN74LVC1G32QDBVRQ1; DBV5 SN74LVC1G3T2Q
U6: PD2328J5050S2HF
U7: LTC5505-1ES5; TSOT-23-5

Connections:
5VA: C1.1, C3.1, C7.1, C12.1, J2.1, J2.2, J3.1, R1.2, R5.2, R6.2, U3.5 (VCC), U7.5 (VCC)
/PWR_DET_IN: U6.6 (OUTPUT2), U7.1 (RFIN)
/PWR_DET_OUT: J5.1, U7.4 (VOUT)
/RF_ATTEN1_OUT1: FL2.1 (INPUT), U2.2
/RF_ATTEN2_OUT1: C8.1, U4.2
/RF_ATTEN2_OUT2: C8.2, U5.2 (RF_IN)
/RF_BPF2_OUT: FL2.4 (OUTPUT), U4.1
/RF_BPF_OUT1: C2.1, FL1.4 (OUTPUT)
/RF_BPF_OUT2: C2.2, U1.2 (RF_IN)
/RF_IN: FL1.1 (INPUT), J1.3
/RF_LNA1_OUT1: C5.1, L1.2, U1.7 (RF_OUT)
/RF_LNA1_OUT2: C5.2, U2.1
/RF_LNA2_OUT1: C9.1, L2.2, U5.7 (RF_OUT)
/RF_LNA2_OUT2: C9.2, U6.2 (INPUT)
/RF_OUT1: J4.3, U6.4 (OUTPUT1)
GND: C1.2, C3.2, C4.2, C6.2, C7.2, C10.2, C11.2, C12.2, FL1.2 (GND), FL1.3 (GND), FL1.5 (GND), FL2.2 (GND), FL2.3 (GND), FL2.5 (GND), J1.1 (In), J1.2 (Ext), J2.3, J2.4, J4.1 (In), J4.2 (Ext), J5.2, R2.1, R3.1, U1.9 (GND), U2.3, U3.3 (GND), U4.3, U5.9 (GND), U6.1 (GND), U6.3 (GND), U6.5 (GND), U7.2 (GND)
unnamed: C4.1, C6.1, L1.1, R1.1
unnamed: C10.1, C11.1, L2.1, R5.1
unnamed: J3.2, R2.2, U3.1 (A), U3.2 (B)
unnamed: R3.2, R4.1, U1.6 (SHUT_DOWN), U5.6 (SHUT_DOWN)
unnamed: R4.2, U3.4 (Y)
unnamed: R6.1, U7.3 (~SHDN)
